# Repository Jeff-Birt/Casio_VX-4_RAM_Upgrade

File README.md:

# Casio_VX-4_RAM_Upgrade
NOTE: I would not reccomend making PCBs form the current posted version. I found the zebra strip contact
pads were about 0.5mm too far from end to end. This was the result of an odd problem with Eagle where
it was reading from a 'part.lbr. file in the project directory when editing the footprint but from the
component library when gnerating the PCB. I have fixed the PCB and have some new ones ordered. I will
upload the new PCB version after I'm able to build and test a few boards.

Internal and external RAM upgrades for Casio VX-4 and similar models. RP-33 clone.

The RP-33 works in the following Casio models: RP-33 works with: FX-840P, FX-841P, FX-850P, FX-860P, 
FX-860Pvc, FX-870P, FX-880P, FX-890P, VX-1, VX-2, VX-3, VX-4, Z-1, Z-1GR, PB2000C and AI-1000

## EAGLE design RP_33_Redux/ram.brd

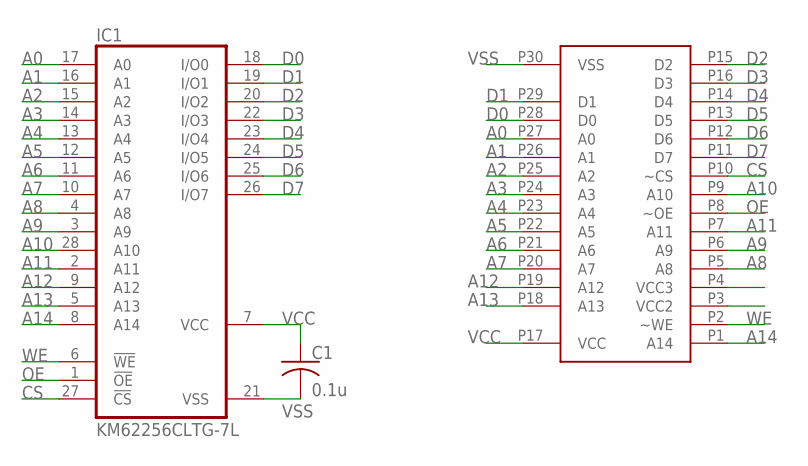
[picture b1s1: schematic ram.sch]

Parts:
C1: 0.1u; C0603
IC1: KM62256CLTG-7L; TSOP1-28
U$1: RAMPORT; CASIORAM

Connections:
A0: IC1.17 (A0), U$1.P27 (A0)
A1: IC1.16 (A1), U$1.P26 (A1)
A2: IC1.15 (A2), U$1.P25 (A2)
A3: IC1.14 (A3), U$1.P24 (A3)
A4: IC1.13 (A4), U$1.P23 (A4)
A5: IC1.12 (A5), U$1.P22 (A5)
A6: IC1.11 (A6), U$1.P21 (A6)
A7: IC1.10 (A7), U$1.P20 (A7)
A8: IC1.4 (A8), U$1.P5 (A8)
A9: IC1.3 (A9), U$1.P6 (A9)
A10: IC1.28 (A10), U$1.P9 (A10)
A11: IC1.2 (A11), U$1.P7 (A11)
A12: IC1.9 (A12), U$1.P19 (A12)
A13: IC1.5 (A13), U$1.P18 (A13)
A14: IC1.8 (A14), U$1.P1 (A14)
CS: IC1.27 (!CS), U$1.P10 (~CS)
D0: IC1.18 (I/O0), U$1.P28 (D0)
D1: IC1.19 (I/O1), U$1.P29 (D1)
D2: IC1.20 (I/O2), U$1.P15 (D2)
D3: IC1.22 (I/O3), U$1.P16 (D3)
D4: IC1.23 (I/O4), U$1.P14 (D4)
D5: IC1.24 (I/O5), U$1.P13 (D5)
D6: IC1.25 (I/O6), U$1.P12 (D6)
D7: IC1.26 (I/O7), U$1.P11 (D7)
OE: IC1.1 (!OE), U$1.P8 (~OE)
VCC: C1.1, IC1.7 (VCC), U$1.P17 (VCC)
VSS: C1.2, IC1.21 (VSS), U$1.P30 (VSS)
WE: IC1.6 (!WE), U$1.P2 (~WE)

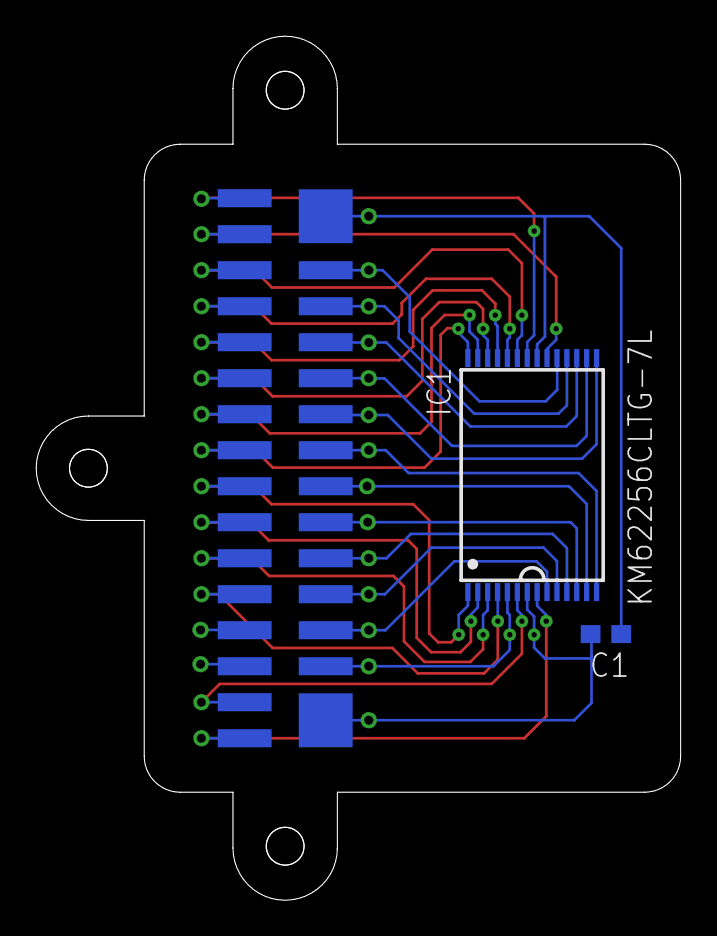
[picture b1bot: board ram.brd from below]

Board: 2 copper layers, 35.8 x 48.0 mm, 3 parts (2 on the bottom side), 28 nets.

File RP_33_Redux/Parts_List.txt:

Name	Qty	Part#				Notes
PCB1 	1 	RP-33 redux PCB 					
IC1  	1 	KM62256CLTG-7L			Forward pinout, low power
C1   	1 	0.1uf 0603 capacitor
SCRW1	3	1.7mmx0.35x3 pan head screw	4mm length OK too
SHM1	1	3D printed shim

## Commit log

2022-03-06 Added PDF for internal upgrade
2022-03-07 Added PDF covering building of RP-33
2022-03-07 Added RP-33 compatibility
2022-03-07 Updated PDF to include RP-33 compatibility
2022-03-15 Update README.md
    Added note
